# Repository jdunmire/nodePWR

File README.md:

TLPHnode
=========
This is a [KiCad](http://kicad-pcb.org/) project for power supply and
breakout board to be used with the TLPHnode.

Additional information about the TLPHnode can be found at the 
[Sensor Nodes](http://sensornodeinfo.rockingdlabs.com) website.

Copyright Jerry Dunmire 2016.

This documentation describes Open Hardware and is licensed under the
CERN OHL v. 1.2.

You may redistribute and modify this documentation under the terms of
the CERN OHL v.1.2. (LICENSE.txt). This documentation is distributed
WITHOUT ANY EXPRESS OR IMPLIED WARRANTY, INCLUDING OF MERCHANTABILITY,
SATISFACTORY QUALITY AND FITNESS FOR A PARTICULAR PURPOSE. Please see
the CERN OHL v.1.2 for applicable conditions

Guidelines on how to apply the CERN OHL v1.2 are in the
cern_ohl_v_1_2_howto.pdf file.

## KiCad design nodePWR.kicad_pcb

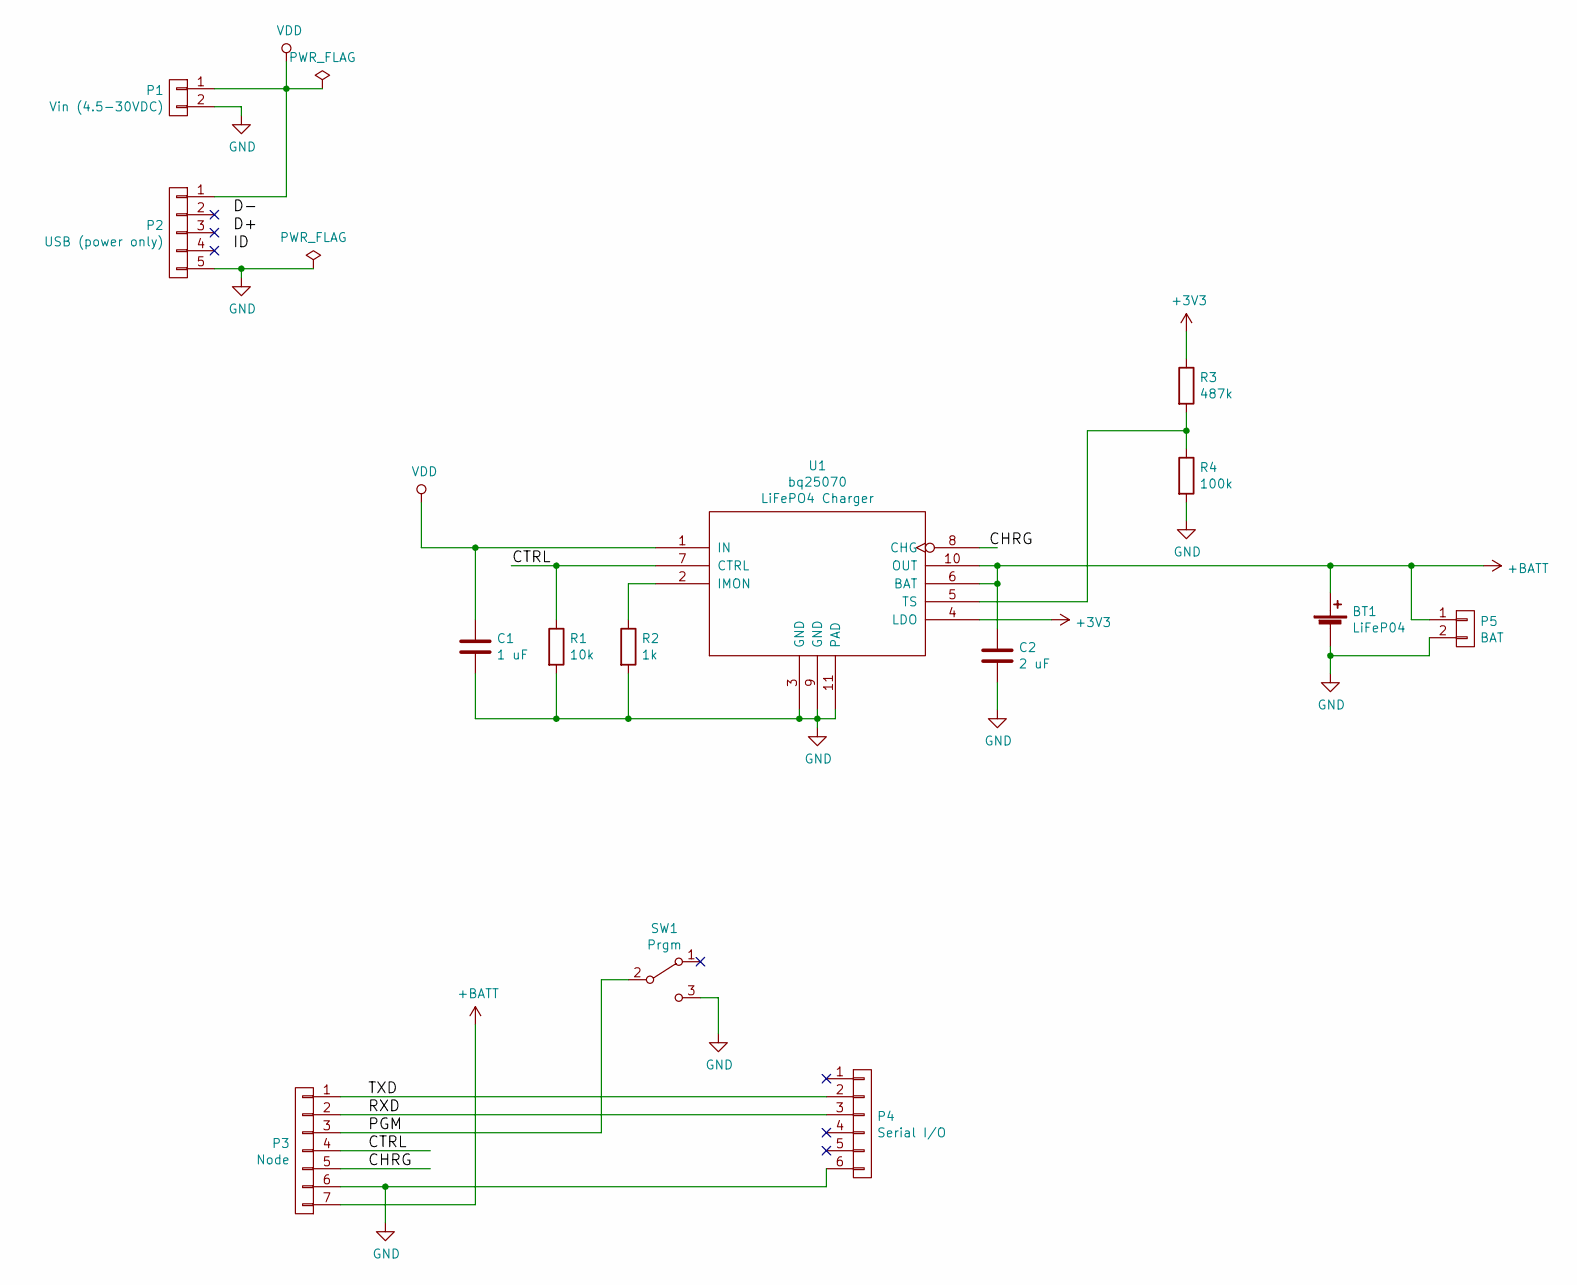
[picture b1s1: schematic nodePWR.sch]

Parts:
BT1: LiFeP04; JST_PH_S2B-PH-SM4-TB_02x2.00mm_Angled
C1: 1 uF; C_0603
C2: 2 uF; C_0603
P1: Vin (4.5-30VDC); Pin_Header_Straight_1x02
P2: USB (power only); USB_Micro-B_10103594-0001LF
P3: Node; FPC_conn-7_8x4.9mm_Pitch0.5mm
P4: Serial I/O; Pin_Header_Straight_1x06
P5: BAT; Pin_Header_Straight_1x02
R1: 10k; R_0603
R2: 1k; R_0603
R3: 487k; R_0603
R4: 100k; R_0603
SW1: Prgm; SW_SPDT_PCM12
U1: bq25070; bq25070_DQC_10-DQC10_P84X2P4

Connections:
+3V3: R3.1, U1.4 (LDO)
+BATT: BT1.1 (+), C2.1, P3.7, P5.1, U1.6 (BAT), U1.10 (OUT)
/CHRG: P3.5, U1.8 (CHG)
/CTRL: P3.4, R1.1, U1.7 (CTRL)
/PGM: P3.3, SW1.2 (B)
/RXD: P3.2, P4.3
/TXD: P3.1, P4.2
GND: BT1.2 (-), C1.2, C2.2, P1.2, P2.5, P3.6, P4.6, P5.2, R1.2, R2.2, R4.2, SW1.3 (C), U1.3 (GND), U1.9 (GND), U1.11 (PAD)
unnamed: R2.1, U1.2 (IMON)
unnamed: R3.2, R4.1, U1.5 (TS)
VDD: C1.1, P1.1, P2.1, U1.1 (IN)

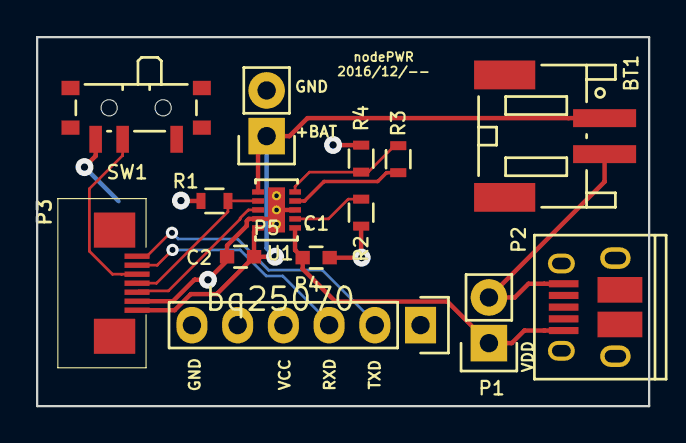
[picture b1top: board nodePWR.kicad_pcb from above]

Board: 2 copper layers, 34.0 x 20.5 mm, 14 parts (0 on the bottom side), 11 nets.

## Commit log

2016-12-12 Setup an empty KiCad project
    On branch master
    Changes to be committed:
    new file: .gitignore
    new file: CAM/README.md
    new file: LICENSE.txt
    new file: PRODUCT.txt
2016-12-13 Checkpoint - starting PCB
    On branch master
    modified: nodePWR-cache.lib
    modified: nodePWR.kicad_pcb
    modified: nodePWR.pro
    modified: nodePWR.sch
2016-12-13 Use TI/Ultra-librarian footprint for bq25070
    On branch master
    modified: nodePWR.kicad_pcb
    modified: nodePWR.sch
2016-12-13 Check-point: parts placed
    - board size 20.5mm high to match TLPNode
    On branch master
    modified: nodePWR.kicad_pcb
2016-12-13 Fix bq25070 footprint
    - vias were numbered separately and therefore not connnected to
    ground. Footprint was changed so that the pad and the vias all
    are pin 11.
    On branch master
    modified: nodePWR.kicad_pcb
2016-12-13 Make board cut a polygon
    On branch master
    modified: nodePWR.kicad_pcb
2016-12-14 Checkpoint: routed, no DRC errors
    On branch master
    modified: nodePWR.kicad_pcb
2016-12-14 Add datasheets
    - actually just a script to get the datasheets in order to avoid
    worrying about IP issues.
    On branch master
    new file: datasheets/.gitignore
    new file: datasheets/getdatasheets.sh
2016-12-14 Add net and local library list
    On branch master
    new file: fp-lib-table
    new file: nodePWR.net
2016-12-14 Make changes to allow for an enclosure
    - move USB closer to PCB edge
    - Rotate BT1 so that connector can be used when there is an
    enclosure.
    - Add pins to solder in a battery.
    - change serial I/O header to veritical.
2016-12-15 Cleanup silk screen
    On branch master
    modified: nodePWR.kicad_pcb
2016-12-15 Clean-up tracks and vias
    On branch master
    modified: nodePWR.kicad_pcb
2016-12-16 Change to standard resistor value
    On branch master
    modified: nodePWR.sch
2016-12-23 No intentional changes
    - I think the changes here are a side effect of an update to KiCAD.
    On branch master
    modified: nodePWR.pro
2016-12-28 Checkpoint - remove routing
    - preparing to add 7-pin connector and signals to the TLPHnode
    board.
    On branch addChargerSignals
    modified: nodePWR.kicad_pcb
2016-12-28 Checkpoint - replaced 6pin conn with 7pin
    - Changed signals to provide charge controll and monitoring on P3
2016-12-28 Checkpoint - Re-annotate, fix DRC warnings
    - Renumbered all anotations to eliminate gaps
    - Marked VDD and GND as power
    On branch addChargerSignals
    modified: nodePWR-cache.lib
    modified: nodePWR.sch
2016-12-28 Add footprint for 7pin
    On branch addChargerSignals
    modified: nodePWR.net
    modified: nodePWR.sch
2016-12-28 Checkpoint - routed
    - passes DRC

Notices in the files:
nodePWR.kicad_pcb:
Copyright 2016, J. Dunmire
All Rights reserved.
